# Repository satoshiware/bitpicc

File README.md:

# Quarter Stick
Bitcoin & microcurrency (SHA256D) Miner - Single ASIC Chip - USB 4.0 (Type C) - Built w\ Eagle

Many thanks to Sidehack (gekkoscience), Kano (cgminer), and Skot (bitaxe)!!
Even though they did not contribute to this project directly, It would not have been possible without their pioneering efforts.

## Setup for Testing Chips
https://youtube.com/watch?v=U-l4Qi08SAI&feature=share

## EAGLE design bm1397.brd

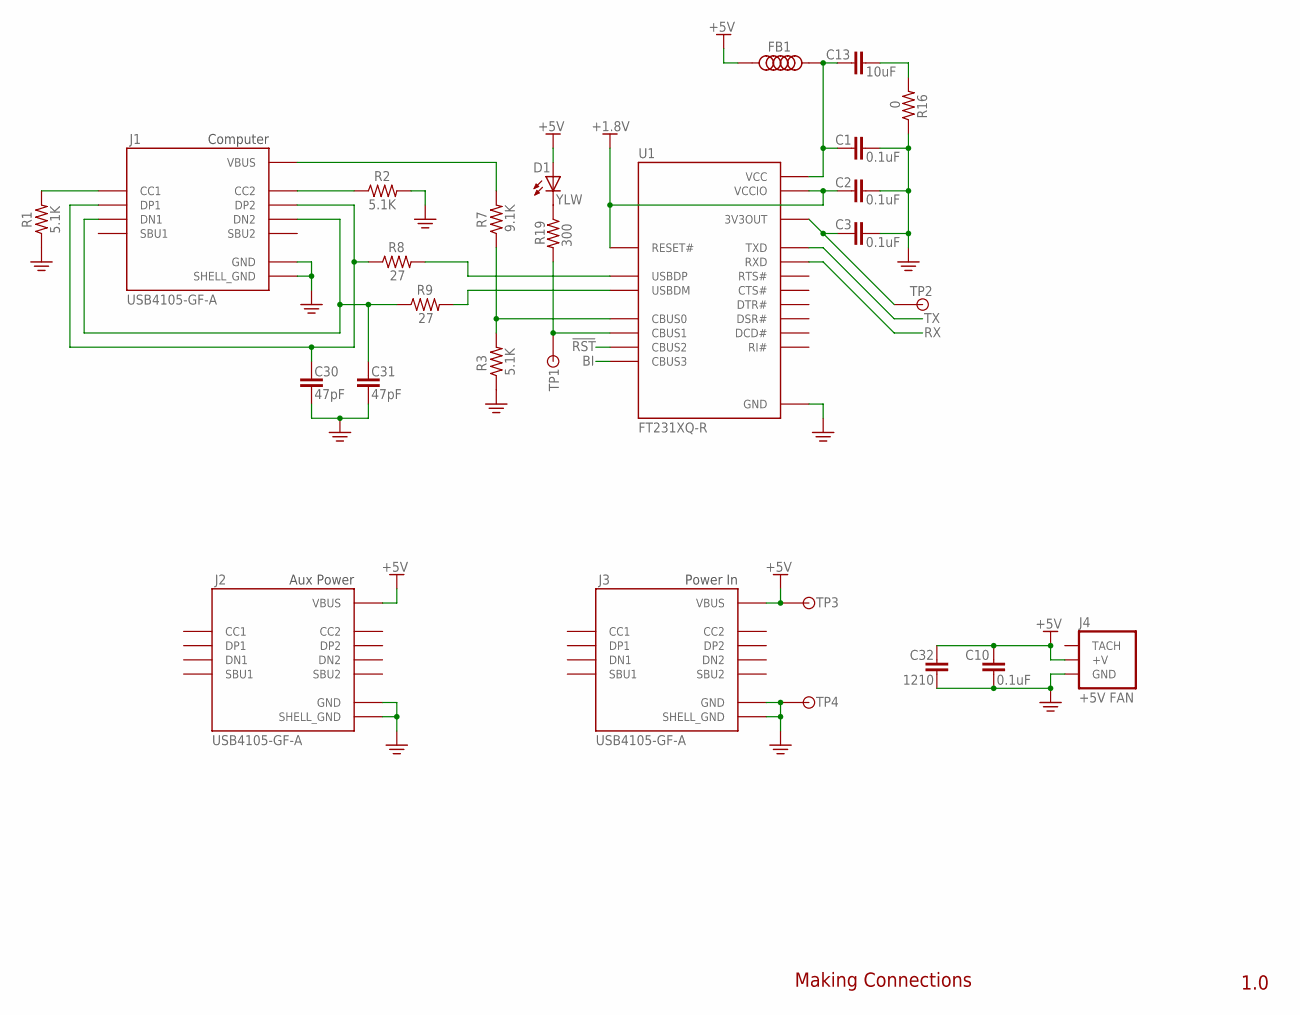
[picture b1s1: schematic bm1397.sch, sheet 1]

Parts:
C1, C2, C3, C10: 0.1uF; C0402
C13: 10uF; C0805
C30, C31: 47pF; C0402
C32: 1210; C1210
D1: YLW; 0805_SD_MNT
FB1: FERRITE_BEADF0402; F0402
J1, J2, J3: USB4105-GF-A; GCT_USB4105-GF-A
J4: +5V FAN; 3PIN_LOCK_HEADER
R1, R2, R3: 5.1K; R0402
R7: 9.1K; R0402
R8, R9: 27; R0402
R16: 0; R0402
R19: 300; R0402
TP1, TP2, TP3, TP4: TESTPOINT; 0.035
U1: FT231XQ-R; QFN50P400X400X80-21N

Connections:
!RST: U1.7 (CBUS2); also elsewhere on the board
+1V8: C2.1, U1.11 (RESET#), U1.20 (VCCIO); also elsewhere on the board
+5V: C10.2, C32.1, D1.A, FB1.1, J2.A4_B9 (VBUS), J2.B4_A9 (VBUS), J3.A4_B9 (VBUS), J3.B4_A9 (VBUS), J4.2 (+V), TP3.TP; also elsewhere on the board
BI: U1.16 (CBUS3); also elsewhere on the board
CC1: J1.A5 (CC1), R1.2
CC2: J1.B5 (CC2), R2.1
FB+5V: C1.1, C13.1, FB1.2, U1.12 (VCC)
GND: C1.2, C2.2, C3.2, C10.1, C30.1, C31.1, C32.2, J1.A1_B12 (GND), J1.B1_A12 (GND), J1.S1 (SHELL_GND), J1.S2 (SHELL_GND), J1.S3 (SHELL_GND), J1.S4 (SHELL_GND), J2.A1_B12 (GND), J2.B1_A12 (GND), J2.S1 (SHELL_GND), J2.S2 (SHELL_GND), J2.S3 (SHELL_GND), J2.S4 (SHELL_GND), J3.A1_B12 (GND), J3.B1_A12 (GND), J3.S1 (SHELL_GND), J3.S2 (SHELL_GND), J3.S3 (SHELL_GND), J3.S4 (SHELL_GND), J4.1 (GND), R1.1, R2.2, R3.1, R16.1, TP4.TP, U1.3 (GND), U1.13 (GND), U1.21 (GND); also elsewhere on the board
unnamed: C13.2, R16.2
unnamed: R8.2, U1.8 (USBDP)
unnamed: C30.2, J1.A6 (DP1), J1.B6 (DP2), R8.1
unnamed: C31.2, J1.A7 (DN1), J1.B7 (DN2), R9.1
unnamed: D1.C, R19.1
unnamed: R9.2, U1.9 (USBDM)
unnamed: R3.2, R7.1, U1.15 (CBUS0)
unnamed: J1.A4_B9 (VBUS), J1.B4_A9 (VBUS), R7.2
unnamed: C3.1, TP2.TP, U1.10 (3V3OUT)
unnamed: R19.2, TP1.TP, U1.14 (CBUS1)
RX: U1.1 (RXD); also elsewhere on the board
TX: U1.17 (TXD); also elsewhere on the board

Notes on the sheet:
Computer
Power In
1.0
Making Connections
Aux Power

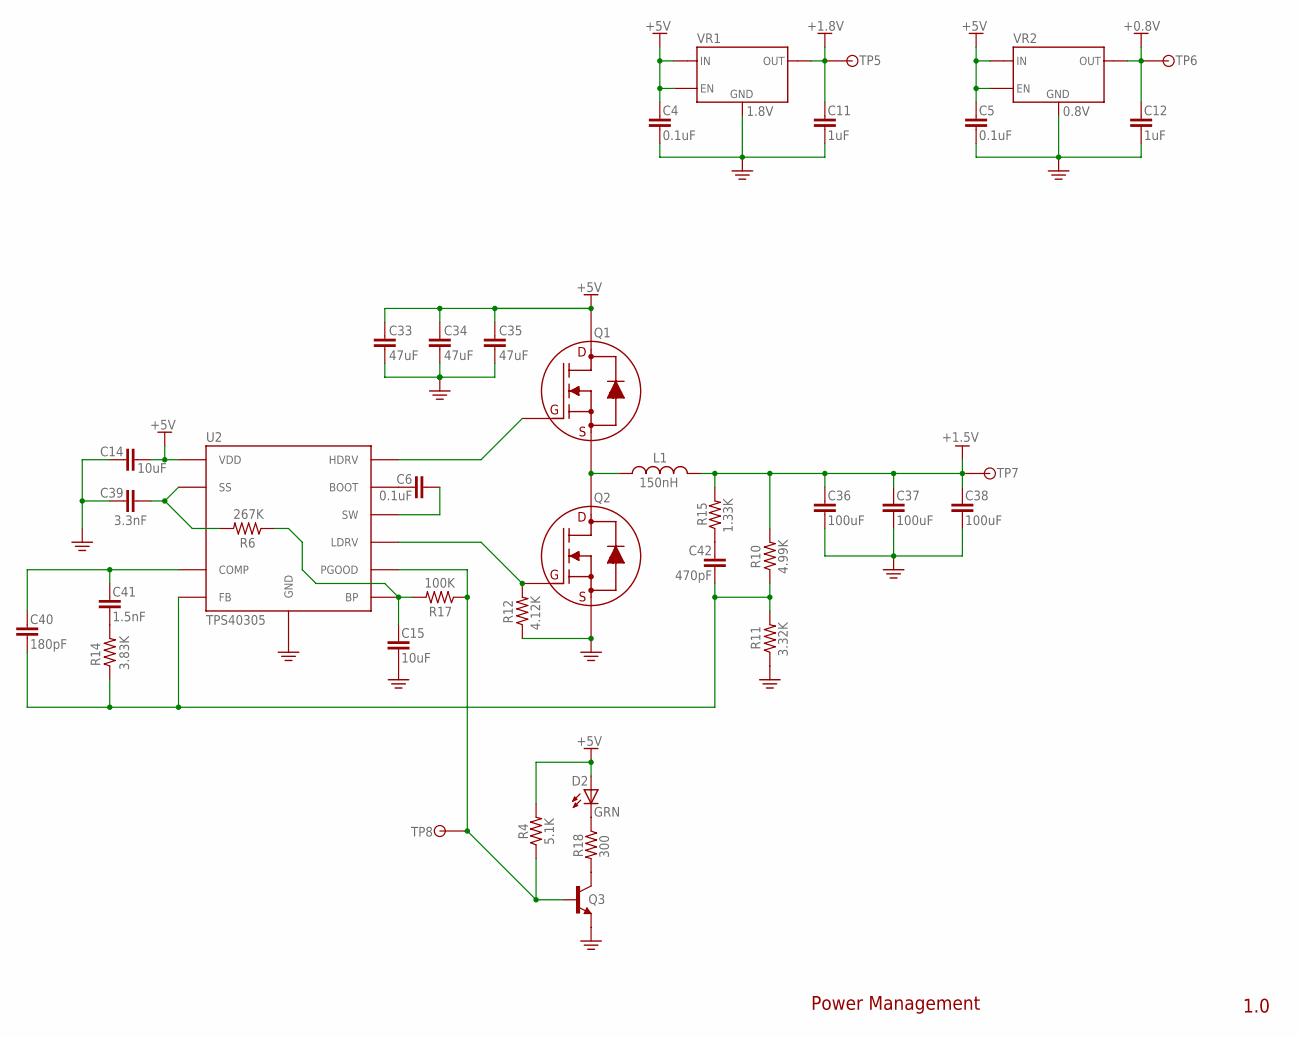
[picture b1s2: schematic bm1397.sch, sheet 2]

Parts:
C4, C5, C6: 0.1uF; C0402
C11, C12: 1uF; C0603
C14, C15: 10uF; C0805
C33, C34, C35: 47uF; C1210
C36, C37, C38: 100uF; C1210
C39: 3.3nF; C0402
C40: 180pF; C0402
C41: 1.5nF; C0402
C42: 470pF; C0402
D2: GRN; 0805_SD_MNT
L1: 150nH; 10.2MMX7.0MM
Q1, Q2: 8-PowerTDFN; CSD17311Q5
Q3: NPN; SOT23
R4: 5.1K; R0402
R6: 267K; R0402
R10: 4.99K; R0402
R11: 3.32K; R0402
R12: 4.12K; R0402
R14: 3.83K; R0402
R15: 1.33K; R0402
R17: 100K; R0402
R18: 300; R0402
TP5, TP6, TP7, TP8: TESTPOINT; 0.035
U2: TPS40305
VR1: 1.8V; TSOP-5
VR2: 0.8V; TSOP-5

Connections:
+0V8: C12.1, TP6.TP, VR2.5 (OUT); also elsewhere on the board
+1V5: C36.1, C37.1, C38.1, L1.2, R10.2, R15.2, TP7.TP; also elsewhere on the board
+1V8: C11.1, TP5.TP, VR1.5 (OUT); also elsewhere on the board
+5V: C4.1, C5.1, C14.1, C33.1, C34.1, C35.1, D2.A, Q1.5 (D), Q1.6 (D), Q1.7 (D), Q1.8 (D), Q1.9 (D), R4.2, U2.1 (VDD), VR1.1 (IN), VR1.3 (EN), VR2.1 (IN), VR2.3 (EN); also elsewhere on the board
BP: C15.1, R6.1, R17.2, U2.10 (BP)
GND: C4.2, C5.2, C11.2, C12.2, C14.2, C15.2, C33.2, C34.2, C35.2, C36.2, C37.2, C38.2, C39.2, Q2.1 (S), Q2.2 (S), Q2.3 (S), Q3.2 (E), R11.1, R12.1, U2.11 (GND), U2.12 (GND), U2.13 (GND), U2.14 (GND), U2.15 (GND), VR1.2 (GND), VR2.2 (GND); also elsewhere on the board
HDRV: Q1.4 (G), U2.7 (HDRV)
LDRV: Q2.4 (G), R12.2, U2.9 (LDRV)
LIN: L1.1, Q1.1 (S), Q1.2 (S), Q1.3 (S), Q2.5 (D), Q2.6 (D), Q2.7 (D), Q2.8 (D), Q2.9 (D)
unnamed: C40.1, C41.1, U2.4 (COMP)
unnamed: C41.2, R14.2
unnamed: C6.2, U2.6 (BOOT)
unnamed: C6.1, U2.8 (SW)
unnamed: C42.1, R15.1
unnamed: C40.2, C42.2, R10.1, R11.2, R14.1, U2.5 (FB)
unnamed: D2.C, R18.1
unnamed: Q3.3 (C), R18.2
PGOOD: Q3.1 (B), R4.1, R17.1, TP8.TP, U2.3 (PGOOD)
SS: C39.1, R6.2, U2.2 (SS)

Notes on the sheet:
1.0
Power Management

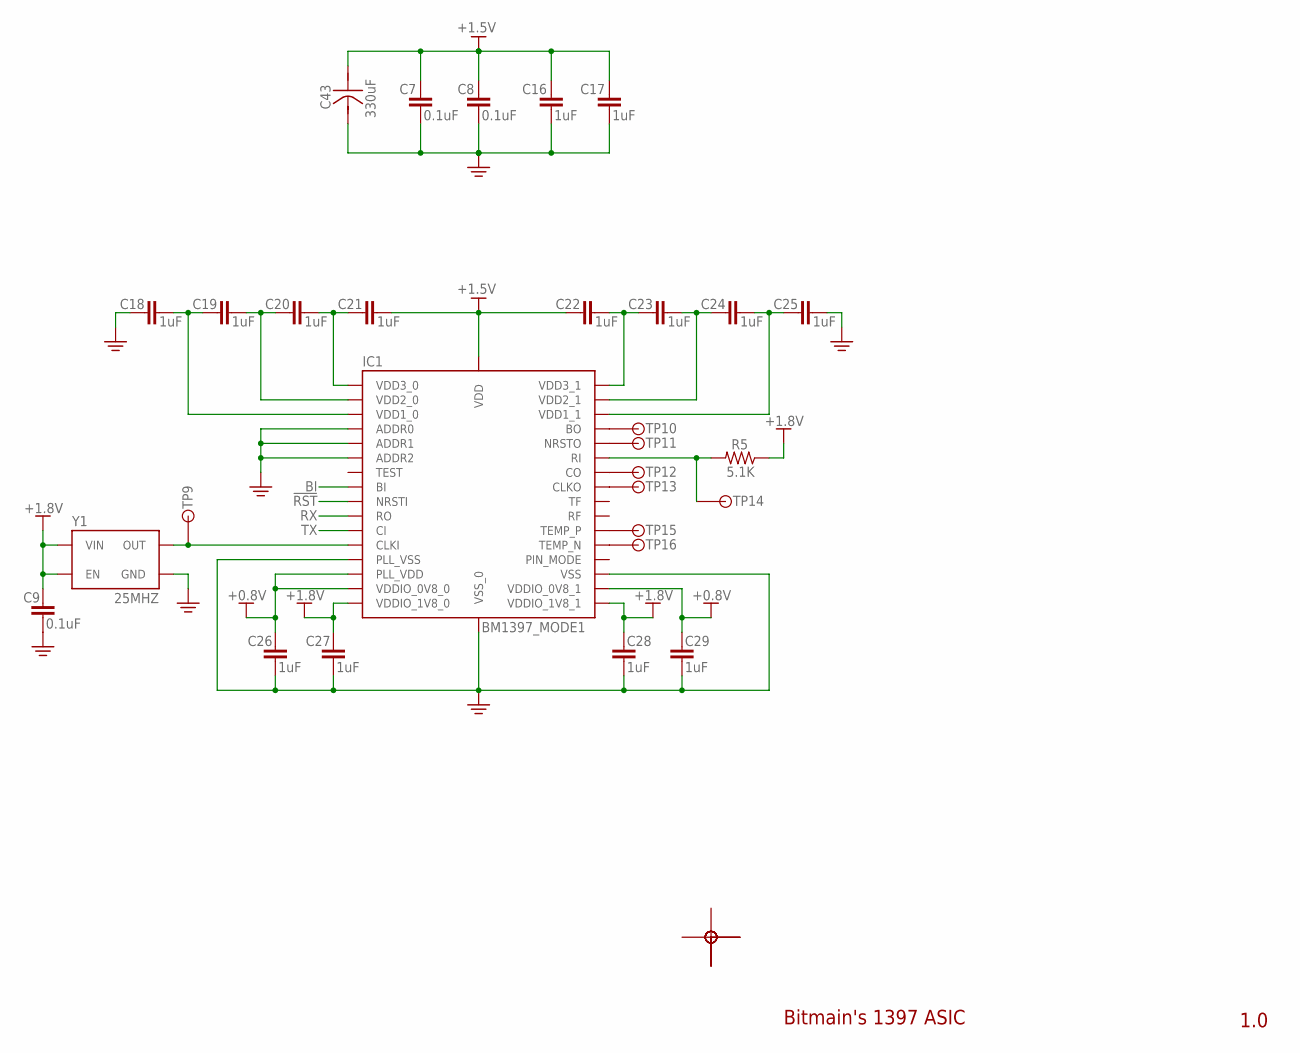
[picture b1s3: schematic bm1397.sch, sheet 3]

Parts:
BOTFIDUCIAL1, BOTFIDUCIAL2, BOTFIDUCIAL3: TESTPOINT; 0.035
C7, C8, C9: 0.1uF; C0402
C16, C17, C18, C19, C20, C21, C22, C23, C24, C25, C26, C27, C28, C29: 1uF; C0603
C43: 330uF; TANT_3.5MMX2.8MM
IC1: BM1397_MODE1; BM1397
R5: 5.1K; R0402
TOPFIDUCIAL1, TOPFIDUCIAL2, TOPFIDUCIAL3: TESTPOINT; 0.035
TP9, TP10, TP11, TP12, TP13, TP14, TP15, TP16: TESTPOINT; 0.035
Y1: 25MHZ; JO32_3.20MMX2.50MM

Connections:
!RST: IC1.9 (NRSTI); also elsewhere on the board
+0V8: C26.1, C29.1, IC1.14 (PLL_VDD), IC1.15 (VDDIO_0V8_0), IC1.18 (VDDIO_0V8_1); also elsewhere on the board
+1V5: C7.2, C8.2, C16.2, C17.2, C21.2, C22.2, C43.A (+), IC1.33 (VDD); also elsewhere on the board
+1V8: C9.2, C27.1, C28.1, IC1.16 (VDDIO_1V8_0), IC1.17 (VDDIO_1V8_1), R5.1, Y1.1 (EN), Y1.4 (VIN); also elsewhere on the board
BI: IC1.8 (BI); also elsewhere on the board
CLK: IC1.12 (CLKI), TP9.TP, Y1.3 (OUT)
GND: C7.1, C8.1, C9.1, C16.1, C17.1, C18.1, C25.1, C26.2, C27.2, C28.2, C29.2, C43.C (-), IC1.4 (ADDR0), IC1.5 (ADDR1), IC1.6 (ADDR2), IC1.13 (PLL_VSS), IC1.19 (VSS), IC1.34 (VSS_0), Y1.2 (GND); also elsewhere on the board
unnamed: BOTFIDUCIAL2.TP, TOPFIDUCIAL1.TP
unnamed: C19.2, C20.1, IC1.2 (VDD2_0)
unnamed: BOTFIDUCIAL3.TP, TOPFIDUCIAL3.TP
unnamed: C18.2, C19.1, IC1.3 (VDD1_0)
unnamed: C20.2, C21.1, IC1.1 (VDD3_0)
unnamed: C22.1, C23.2, IC1.32 (VDD3_1)
unnamed: C23.1, C24.2, IC1.31 (VDD2_1)
unnamed: C24.1, C25.2, IC1.30 (VDD1_1)
unnamed: IC1.21 (TEMP_N), TP16.TP
unnamed: IC1.22 (TEMP_P), TP15.TP
unnamed: IC1.25 (CLKO), TP13.TP
unnamed: IC1.26 (CO), TP12.TP
unnamed: IC1.27 (RI), R5.2, TP14.TP
unnamed: IC1.28 (NRSTO), TP11.TP
unnamed: IC1.29 (BO), TP10.TP
RX: IC1.10 (RO); also elsewhere on the board
TX: IC1.11 (CI); also elsewhere on the board

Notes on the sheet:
1.0
Bitmain's 1397 ASIC

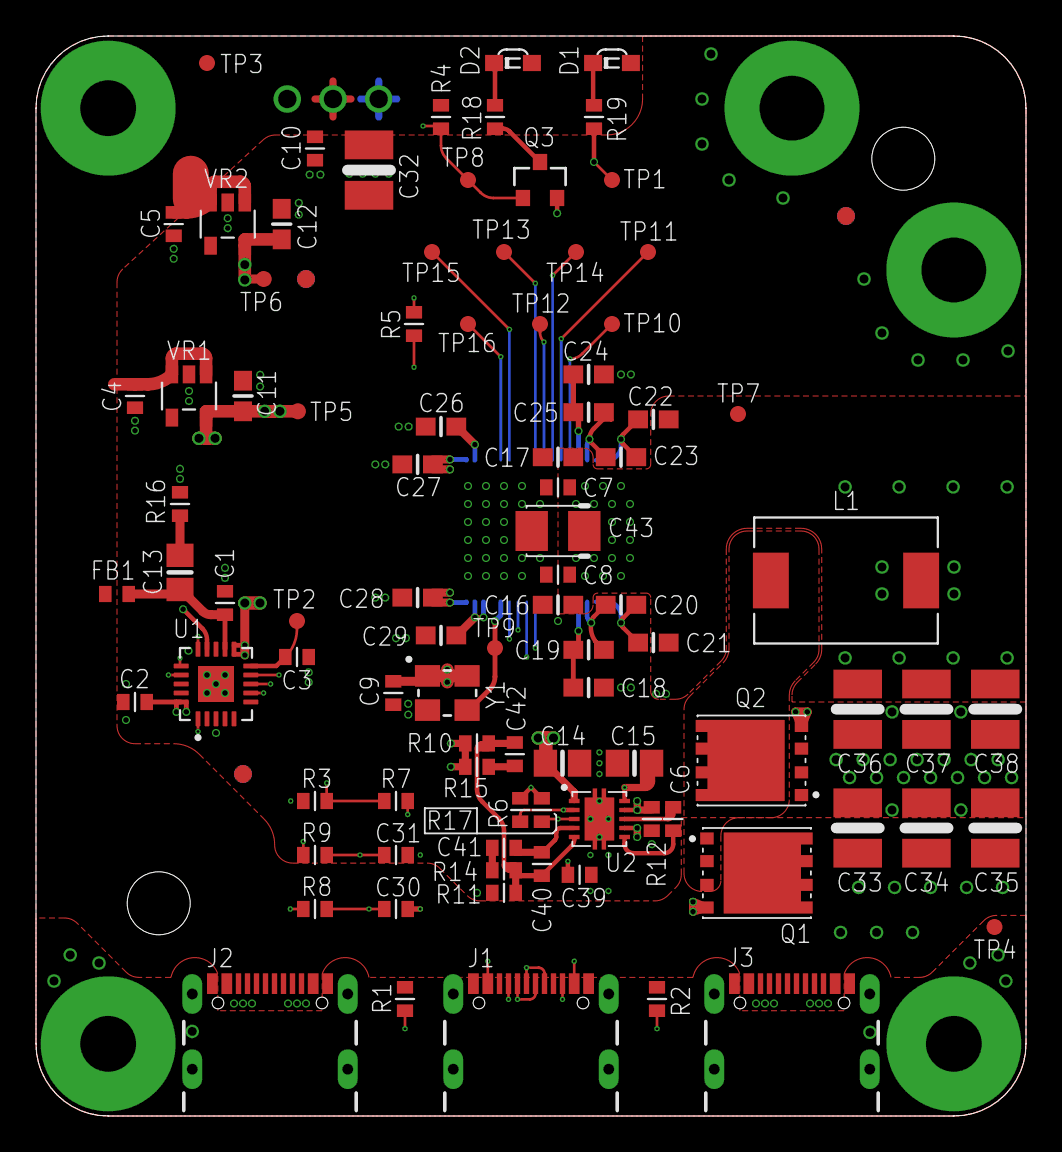
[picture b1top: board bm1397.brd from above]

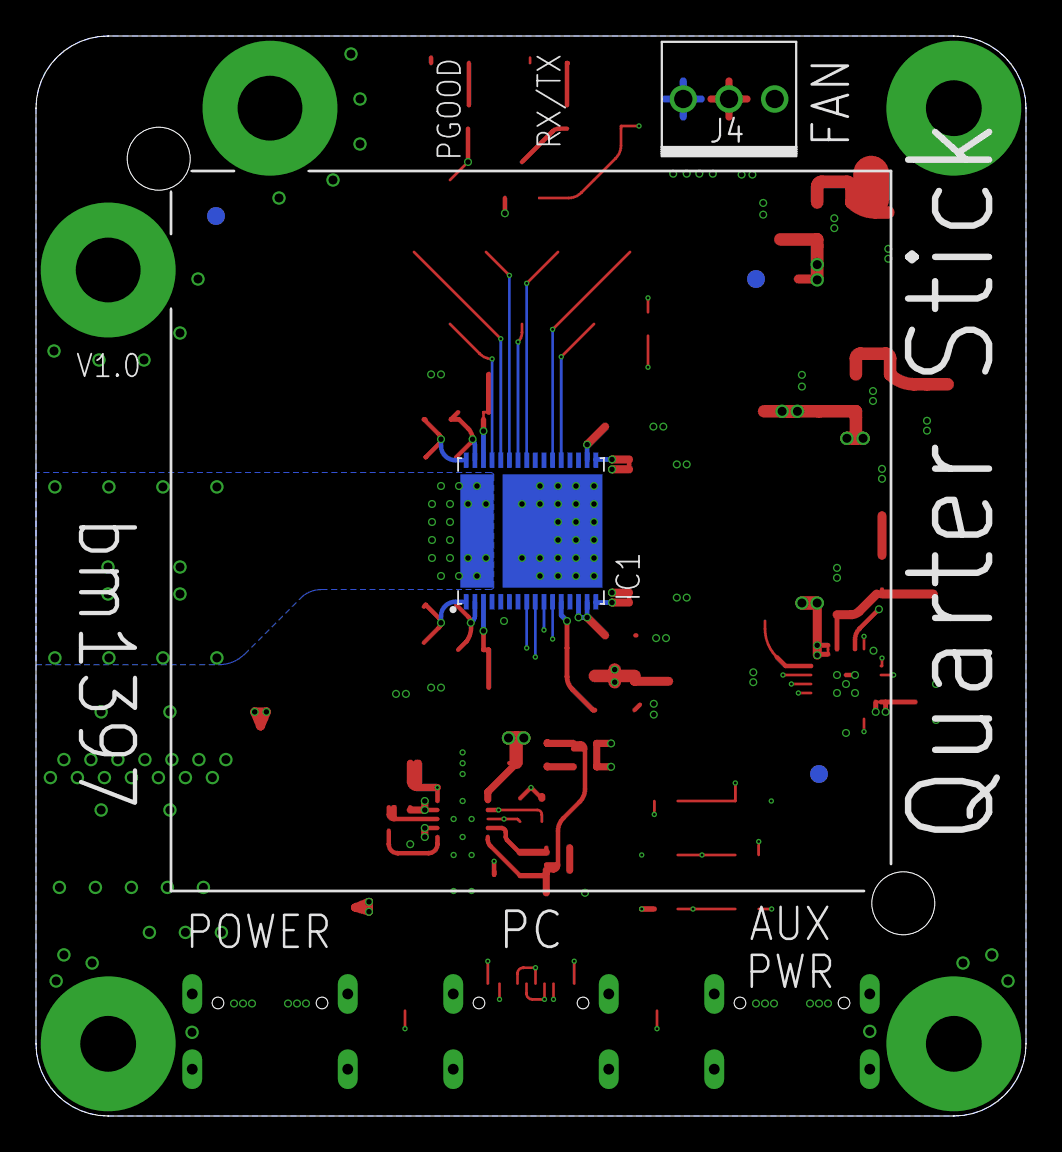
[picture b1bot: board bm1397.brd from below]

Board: 4 copper layers, 55.0 x 60.0 mm, 100 parts (5 on the bottom side), 52 nets.

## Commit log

2023-07-11 Changed name to "Quarter Stick"
2023-08-07 Updated Fan Connector
2023-08-07 Updated Fan Connector: 22-23-2031
